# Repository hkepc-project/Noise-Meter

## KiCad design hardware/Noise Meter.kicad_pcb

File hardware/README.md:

This repository contains a Noise Meter project from the following link:

http://www.hkepc.com/forum/viewthread.php?fid=146&tid=2419038&extra=page%3D1

The hardware and associated materials (excluding any software) are provided under a [CC BY-SA 4.0](https://creativecommons.org/licenses/by-sa/4.0/) license.

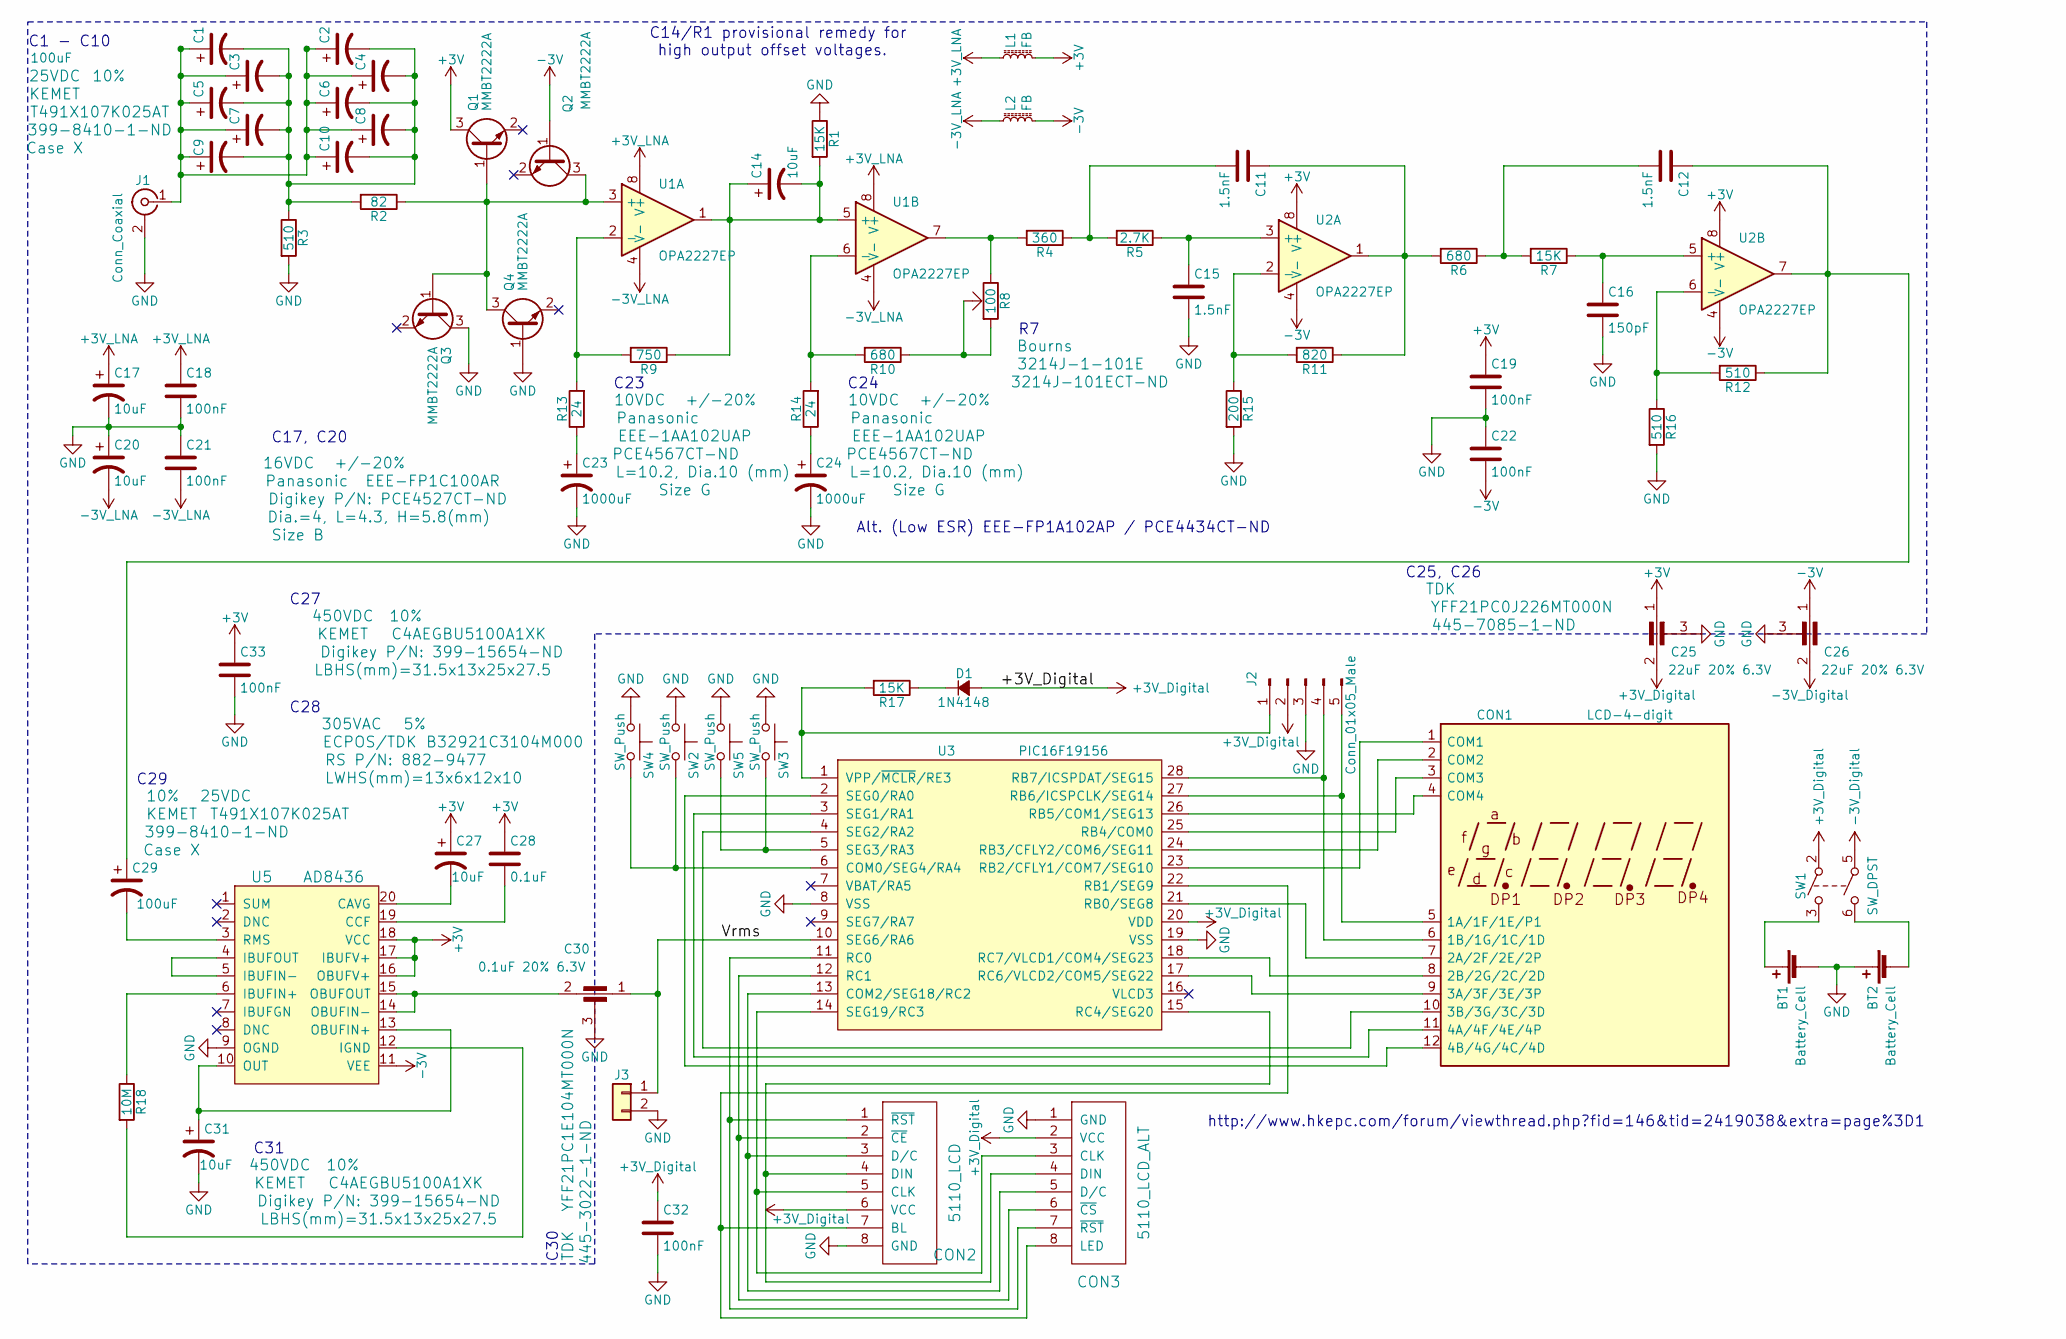
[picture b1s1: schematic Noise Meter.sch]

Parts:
BT1, BT2: Battery_Cell; Keystone_1058_1x2032-CoinCell
C1, C2, C3, C4, C5, C6, C7, C8, C9, C10, C29: 100uF; CP_Tantalum_Case-X_EIA-7343-43_Hand; Tolerance 10%; Voltage 25VDC; Manufacturer P/N T491X107K025AT; Digikey P/N 399-8410-1-ND
C11, C12, C15: 1.5nF; C_0603_HandSoldering
C14, C17, C20: 10uF; CP_Elec_4x4.5; Voltage 16VDC; Tolerance +/-20%; Manufacturer P/N EEE-FP1C100AR; Digikey P/N Digikey P/N: PCE4527CT-ND
C16: 150pF; C_0603_HandSoldering
C18, C19, C21, C22, C32, C33: 100nF; C_0603_HandSoldering
C23, C24: 1000uF; CP_Elec_10x10.5; Voltage 10VDC; Tolerance +/-20%; Manufacturer P/N EEE-1AA102UAP; Digikey P/N PCE4567CT-ND
C25, C26: 22uF 20% 6.3V; Feedthrough_C_0805_HandSoldering; Manufacturer P/N YFF21PC0J226MT000N; Digikey P/N 445-7085-1-ND
C27, C31: 10uF; C_Rect_L31.5mm_W13.0mm_P27.50mm_MKS4; Tolerance 10%; Voltage 450VDC; Manufacturer P/N C4AEGBU5100A1XK; Digikey P/N Digikey P/N: 399-15654-ND
C28: 0.1uF; C_Rect_L13.0mm_W6.0mm_P10.00mm_FKS3_FKP3_MKS4; Voltage 305VAC; Tolerance 5%
C30: 0.1uF 20% 6.3V; Feedthrough_C_0805_HandSoldering; Manufacturer P/N YFF21PC1E104MT000N; Digikey P/N 445-3022-1-ND
CON1: LCD-4-digit; 4-digit-LCD-footprint
CON2: 5110_LCD; 5110
CON3: 5110_LCD_ALT; 5110-Alt
D1: 1N4148; D_SOD-123
J1: Conn_Coaxial; SMA-CONN
J2: Conn_01x05_Male; Pin_Header_Angled_1x05_Pitch2.54mm
J3: Conn_01x02; Pin_Header_Angled_1x02_Pitch2.54mm
L1, L2: FB; L_0805
Q1, Q2, Q3, Q4: MMBT2222A; SOT-23
R1, R7, R17: 15K; R_0603_HandSoldering
R2: 82; R_0603_HandSoldering
R3, R12, R16: 510; R_0603_HandSoldering
R4: 360; R_0603_HandSoldering
R5: 2.7K; R_0603_HandSoldering
R6, R10: 680; R_0603_HandSoldering
R8: 100; Potentiometer_Trimmer_Bourns_3214J; Manufacturer P/N 3214J-1-101E; Digikey P/N 3214J-101ECT-ND
R9: 750; R_0603_HandSoldering
R11: 820; R_0603_HandSoldering
R13, R14: 24; R_0603_HandSoldering
R15: 200; R_0603_HandSoldering
R18: 10M; R_0603_HandSoldering
SW1: SW_DPST; SW_CuK_JS202011AQN_DPDT_Angled
SW2, SW3, SW4, SW5: SW_Push; SW_SPST_B3SL-1002P
U1, U2: OPA2227EP; SOIC-8-N
U3: PIC16F19156; SSOP-28_5.3x10.2mm_Pitch0.65mm
U5: AD8436; SSOP-20

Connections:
+3V: C19.1, C25.1, C27.1, C28.1, C33.1, L1.2, Q1.3 (C), U2.8 (V+), U5.16 (OBUFV+), U5.17 (IBUFV+), U5.18 (VCC)
+3V_Digital: C25.2, C32.1, CON2.6 (VCC), CON3.2 (VCC), D1.2 (A), J2.2, SW1.2, U3.20 (VDD)
+3V_LNA: C17.1, C18.1, L1.1, U1.8 (V+)
-3V: C22.2, C26.1, L2.2, Q2.1 (B), U2.4 (V-), U5.11 (VEE)
-3V_Digital: C26.2, SW1.5
-3V_LNA: C20.2, C21.2, L2.1, U1.4 (V-)
/Vrms: C30.1, J3.1, U3.10 (SEG6/RA6)
GND: BT1.2 (-), BT2.1 (+), C15.2, C16.2, C17.2, C18.2, C19.2, C20.1, C21.1, C22.1, C23.2, C24.2, C25.3, C26.3, C30.3, C31.2, C32.2, C33.2, CON2.8 (GND), CON3.1 (GND), J1.2 (Ext), J2.3, J3.2, Q3.3 (C), Q4.1 (B), R1.1, R3.2, R15.2, R16.2, SW2.1, SW3.1, SW4.1, SW5.1, U3.8 (VSS), U3.19 (VSS), U5.9 (OGND)
unnamed: BT1.1 (+), SW1.3
unnamed: BT2.2 (-), SW1.6
unnamed: C1.1, C2.1, C3.1, C4.1, C5.1, C6.1, C7.1, C8.1, C9.1, C10.1, J1.1 (In)
unnamed: C1.2, C2.2, C3.2, C4.2, C5.2, C6.2, C7.2, C8.2, C9.2, C10.2, R2.2, R3.1
unnamed: C11.1, R6.2, R11.1, U2.1
unnamed: C11.2, R4.1, R5.2
unnamed: C12.1, C29.1, R12.1, U2.7
unnamed: C12.2, R6.1, R7.2
unnamed: C14.1, C14.2, R1.2, R9.1, U1.1, U1.5 (+)
unnamed: C15.1, R5.1, U2.3 (+)
unnamed: C16.1, R7.1, U2.5 (+)
unnamed: C23.1, R13.1
unnamed: C24.1, R14.1
unnamed: C27.2, U5.20 (CAVG)
unnamed: C28.2, U5.19 (CCF)
unnamed: C29.2, U5.3 (RMS)
unnamed: C30.2, U5.14 (OBUFIN-), U5.15 (OBUFOUT)
unnamed: C31.1, U5.10 (OUT), U5.13 (OBUFIN+)
unnamed: CON1.1 (COM1), U3.23 (RB2/CFLY1/COM7/SEG10)
unnamed: CON1.2 (COM2), U3.24 (RB3/CFLY2/COM6/SEG11)
unnamed: CON1.3 (COM3), U3.25 (RB4/COM0)
unnamed: CON1.4 (COM4), U3.26 (RB5/COM1/SEG13)
unnamed: CON1.5 (1A/1F/1E/P1), J2.5, U3.27 (RB6/ICSPCLK/SEG14)
unnamed: CON1.6 (1B/1G/1C/1D), J2.4, U3.28 (RB7/ICSPDAT/SEG15)
unnamed: CON1.7 (2A/2F/2E/2P), U3.21 (RB0/SEG8)
unnamed: CON1.8 (2B/2G/2C/2D), U3.18 (RC7/VLCD1/COM4/SEG23)
unnamed: CON1.9 (3A/3F/3E/3P), U3.17 (RC6/VLCD2/COM5/SEG22)
unnamed: CON1.10 (3B/3G/3C/3D), U3.4 (SEG2/RA2)
unnamed: CON1.11 (4A/4F/4E/4P), U3.3 (SEG1/RA1)
unnamed: CON1.12 (4B/4G/4C/4D), U3.2 (SEG0/RA0)
unnamed: CON2.1 (~RST), CON3.7 (~RST), U3.11 (RC0)
unnamed: CON2.2 (~CE), CON3.6 (~CS), U3.12 (RC1)
unnamed: CON2.3 (D/C), CON3.5 (D/C), U3.13 (COM2/SEG18/RC2)
unnamed: CON2.4 (DIN), CON3.4 (DIN), U3.15 (RC4/SEG20)
unnamed: CON2.5 (CLK), CON3.3 (CLK), U3.14 (SEG19/RC3)
unnamed: CON2.7 (BL), CON3.8 (LED), U3.22 (RB1/SEG9)
unnamed: D1.1 (K), R17.1
unnamed: J2.1, R17.2, U3.1 (VPP/~MCLR~/RE3)
unnamed: Q1.1 (B), Q2.3 (C), Q3.1 (B), Q4.3 (C), R2.1, U1.3 (+)
unnamed: R4.2, R8.1, U1.7
unnamed: R8.2, R8.3, R10.1
unnamed: R10.2, R14.2, U1.6 (-)
unnamed: R11.2, R15.1, U2.2 (-)
unnamed: R12.2, R16.1, U2.6 (-)
unnamed: R9.2, R13.2, U1.2 (-)
unnamed: R18.1, U5.6 (IBUFIN+)
unnamed: R18.2, U5.12 (IGND)
unnamed: SW2.2, SW4.2, U3.6 (COM0/SEG4/RA4)
unnamed: SW3.2, SW5.2, U3.5 (SEG3/RA3)
unnamed: U5.4 (IBUFOUT), U5.5 (IBUFIN-)

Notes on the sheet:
C27
C28
C29
Alt. (Low ESR) EEE-FP1A102AP / PCE4434CT-ND
C17, C20
C31
C24
C23
C25, C26
C30
C1 - C10
C14/R1 provisional remedy for high output offset voltages.
http://www.hkepc.com/forum/viewthread.php?fid=146&tid=2419038&extra=page%3D1

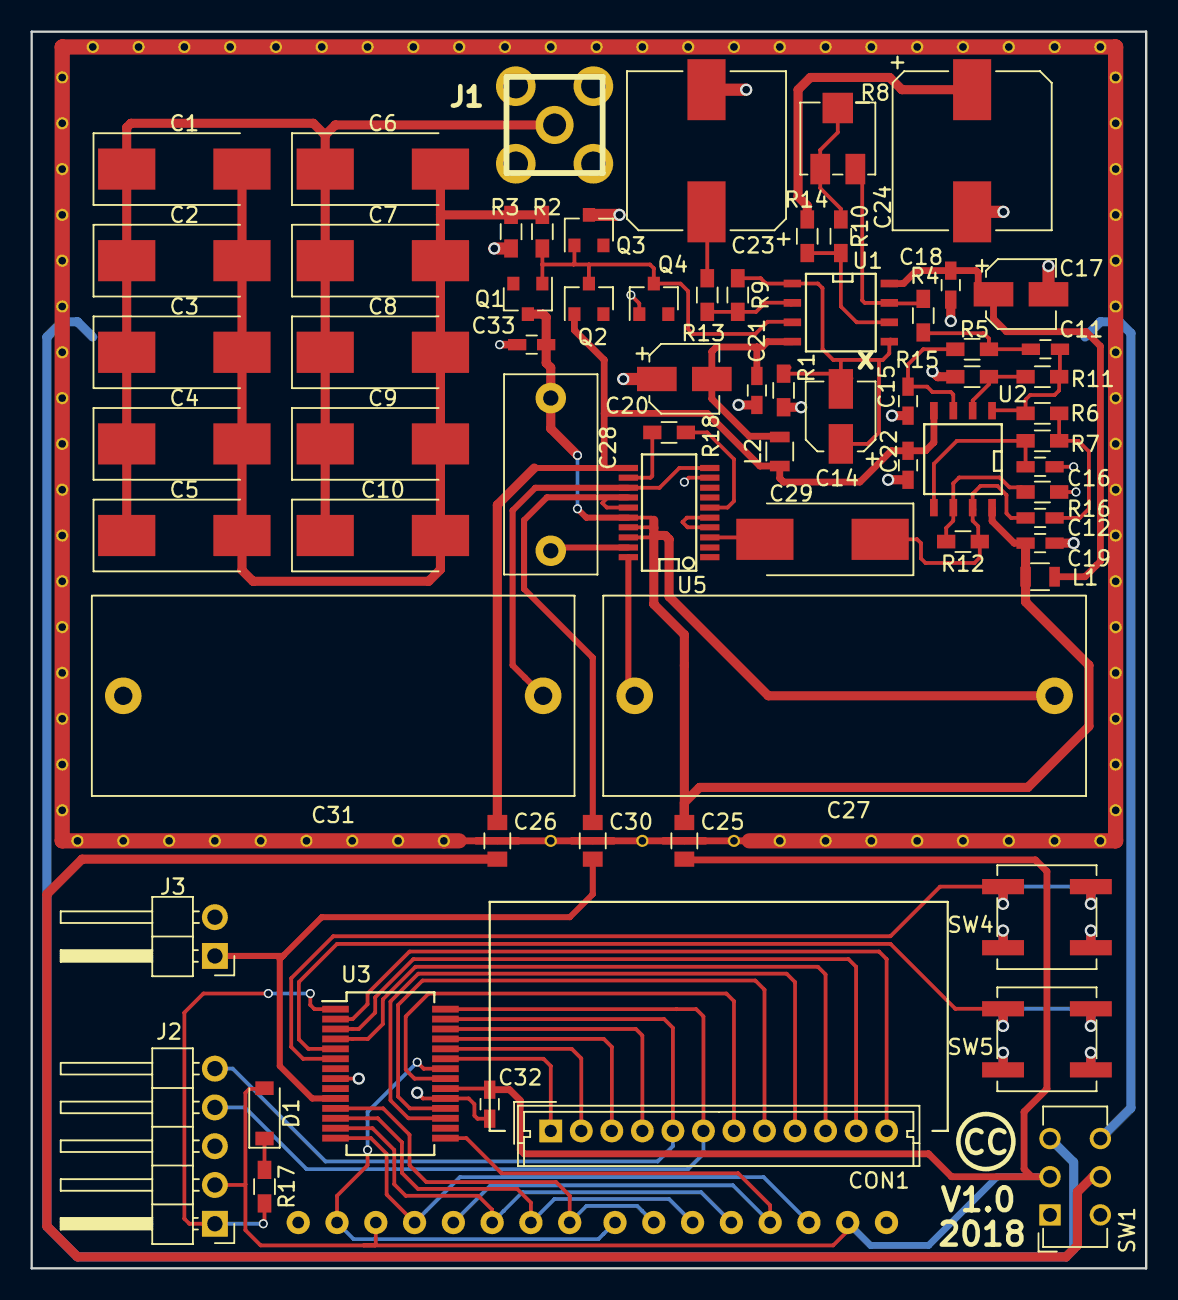
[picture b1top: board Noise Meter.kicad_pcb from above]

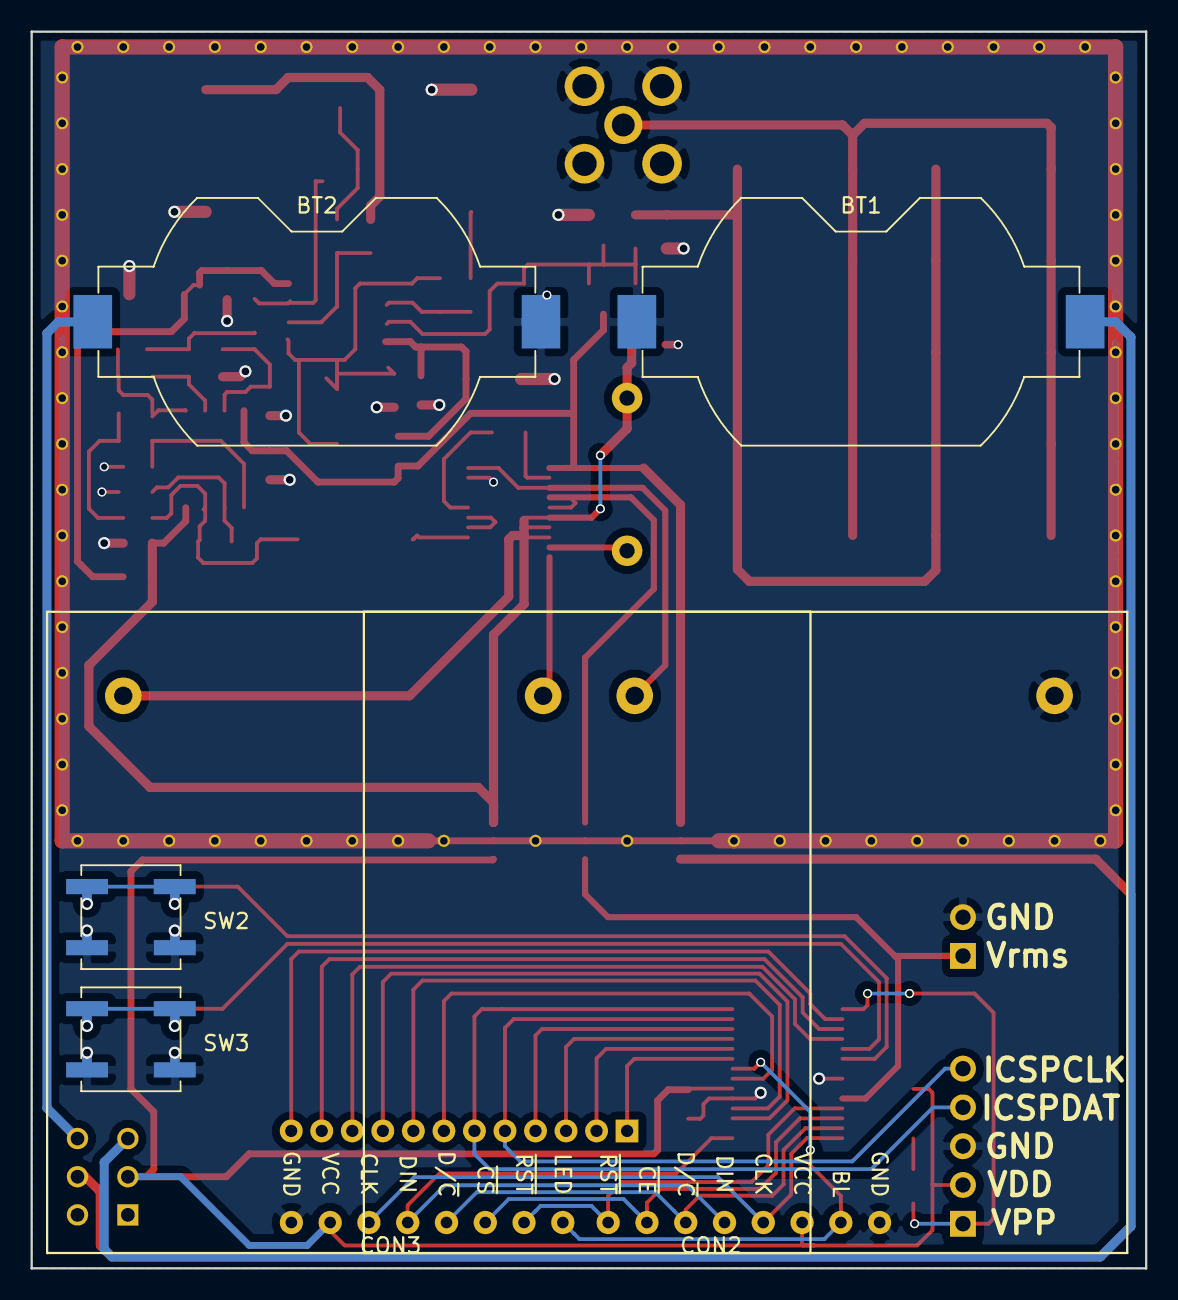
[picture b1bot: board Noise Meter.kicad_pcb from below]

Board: 2 copper layers, 73.0 x 81.0 mm, 74 parts (6 on the bottom side), 58 nets.

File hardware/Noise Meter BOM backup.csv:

Ref,Qty,Value,Footprint,Datasheet,Digikey P/N,EIA Case Code,Manufacturer,Manufacturer P/N,Mnaufacturer P/N,Size,Size Code,Szie,Tolerance,Vendor P/N,Voltage
Title,,,,,,,,,,,,,,,
Revision,,,,,,,,,,,,,,,
Date,,,,,,,,,,,,,,,
Generated,2018-02-01 23:53:58,,,,,,,,,,,,,,
Company,,,,,,,,,,,,,,,
Comment 1,,,,,,,,,,,,,,,
Comment 2,,,,,,,,,,,,,,,
Comment 3,,,,,,,,,,,,,,,
Comment 4,,,,,,,,,,,,,,,
Total Parts,74,,,,,,,,,,,,,,
Total Unique Parts,37,,,,,,,,,,,,,,
,,,,,,,,,,,,,,,
,,,,,,,,,,,,,,,
,,,,,,,,,,,,,,,
Ref,Qty,Value,Footprint,Datasheet,Digikey P/N,EIA Case Code,Manufacturer,Manufacturer P/N,Mnaufacturer P/N,Size,Size Code,Szie,Tolerance,Vendor P/N,Voltage
BT1 BT2 ,2,Battery_Cell,Battery_Holders:Keystone_1058_1x2032-CoinCell,, , , , , , , , , , , 
C1 C2 C3 C4 C5 C6 C7 C8 C9 C10 C29 ,11,100uF,Capacitors_Tantalum_SMD:CP_Tantalum_Case-X_EIA-7343-43_Hand,https://content.kemet.com/datasheets/KEM_T2005_T491.pdf,399-8410-1-ND,,KEMET,T491X107K025AT, , ,Case X, ,10%, ,25VDC
C11 C12 C15 ,3,1.5nF,Capacitors_SMD:C_0603_HandSoldering,, , , , , , , , , , , 
C14 C17 C20 ,3,10uF,Capacitors_SMD:CP_Elec_4x4.5,https://industrial.panasonic.com/cdbs/www-data/pdf/RDE0000/A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,PCE4527CT-ND, ,Panasonic,EEE-FP1C100AR, ,Dia.=4  L=4.3  H=5.8(mm),Size B, ,+/-20%, ,16VDC
C16 ,1,150pF,Capacitors_SMD:C_0603_HandSoldering,, , , , , , , , , , , 
C18 C19 C21 C22 C32 C33 ,6,100nF,Capacitors_SMD:C_0603_HandSoldering,, , , , , , , , , , , 
C23 C24 ,2,1000uF,Capacitors_SMD:CP_Elec_10x10.5,https://industrial.panasonic.com/cdbs/www-data/pdf/RDE0000/A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,PCE4567CT-ND, ,Panasonic,EEE-1AA102UAP, , ,Size G,L=10.2  Dia.10 (mm),+/-20%, ,10VDC
C25 C26 ,2,22uF 20% 6.3V,Noise Meter Kicad Footprint Library:Feedthrough_C_0805_HandSoldering,,445-7085-1-ND, ,TDK,YFF21PC0J226MT000N, , , , , , , 
C27 C31 ,2,10uF,Capacitors_THT:C_Rect_L31.5mm_W13.0mm_P27.50mm_MKS4,https://content.kemet.com/datasheets/KEM_F3103_R60.pdf,399-15654-ND, ,KEMET,C4AEGBU5100A1XK, ,LBHS(mm)=31.5x13x25x27.5, , ,10%, ,450VDC
C28 ,1,0.1uF,Capacitors_THT:C_Rect_L13.0mm_W6.0mm_P10.00mm_FKS3_FKP3_MKS4,https://en.tdk.eu/inf/20/20/db/fc_2009/X2_B32921_928.pdf, , ,ECPOS/TDK,B32921C3104M000,,LWHS(mm)=13x6x12x10, , ,5%,RS P/N: 882-9477,305VAC
C30 ,1,0.1uF 20% 6.3V,Noise Meter Kicad Footprint Library:Feedthrough_C_0805_HandSoldering,https://product.tdk.com/info/en/catalog/datasheets/3tf_comme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,445-3022-1-ND, ,TDK,YFF21PC1E104MT000N, , , , , , , 
CON1 ,1,LCD-4-digit,Noise Meter Kicad Footprint Library:4-digit-LCD-footprint,, , , , , , , , , , , 
CON2 ,1,5110_LCD,Noise Meter Kicad Footprint Library:5110,, , , , , , , , , , , 
CON3 ,1,5110_LCD_ALT,Noise Meter Kicad Footprint Library:5110-Alt,, , , , , , , , , , , 
D1 ,1,1N4148,Diodes_SMD:D_SOD-123,, , , , , , , , , , , 
J1 ,1,Conn_Coaxial,Noise Meter Kicad Footprint Library:SMA-CONN,, , , , , , , , , , , 
J2 ,1,Conn_01x05_Male,Pin_Headers:Pin_Header_Angled_1x05_Pitch2.54mm,, , , , , , , , , , , 
J3 ,1,Conn_01x02,Pin_Headers:Pin_Header_Angled_1x02_Pitch2.54mm,, , , , , , , , , , , 
L1 L2 ,2,FB,Inductors_SMD:L_0805,, , , , , , , , , , , 
Q1 Q2 Q3 Q4 ,4,MMBT2222A,TO_SOT_Packages_SMD:SOT-23,, , , , , , , , , , , 
R1 R7 R17 ,3,15K,Resistors_SMD:R_0603_HandSoldering,, , , , , , , , , , , 
R2 ,1,82,Resistors_SMD:R_0603_HandSoldering,, , , , , , , , , , , 
R3 R12 R16 ,3,510,Resistors_SMD:R_0603_HandSoldering,, , , , , , , , , , , 
R4 ,1,360,Resistors_SMD:R_0603_HandSoldering,, , , , , , , , , , , 
R5 ,1,2.7K,Resistors_SMD:R_0603_HandSoldering,, , , , , , , , , , , 
R6 R10 ,2,680,Resistors_SMD:R_0603_HandSoldering,, , , , , , , , , , , 
R8 ,1,100,Potentiometers:Potentiometer_Trimmer_Bourns_3214J,http://www.bourns.com/docs/Product-Datasheets/3214.pdf,3214J-101ECT-ND, ,Bourns,3214J-1-101E, , , , , , , 
R9 ,1,750,Resistors_SMD:R_0603_HandSoldering,, , , , , , , , , , , 
R11 ,1,820,Resistors_SMD:R_0603_HandSoldering,, , , , , , , , , , , 
R13 R14 ,2,24,Resistors_SMD:R_0603_HandSoldering,, , , , , , , , , , , 
R15 ,1,200,Resistors_SMD:R_0603_HandSoldering,, , , , , , , , , , , 
R18 ,1,10M,Resistors_SMD:R_0603_HandSoldering,, , , , , , , , , , , 
SW1 ,1,SW_DPST,Buttons_Switches_THT:SW_CuK_JS202011AQN_DPDT_Angled,, , , , , , , , , , , 
SW2 SW3 SW4 SW5 ,4,SW_Push,Buttons_Switches_SMD:SW_SPST_B3SL-1002P,, , , , , , , , , , , 
U1 U2 ,2,OPA2227EP,SMD_Packages:SOIC-8-N,,, , TI,OPA2227EP,, , , ,,, 
U3 ,1,PIC16F19156,Housings_SSOP:SSOP-28_5.3x10.2mm_Pitch0.65mm,, , ,microchip,PIC16F19156,, , , ,,, 
U5 ,1,AD8436,SMD_Packages:SSOP-20,, , ,analog,AD8436,, , , ,,, 
,,,,,,,,,,,,,,,
,,,,,,,,,,,,,,,
,,,,,,,,,,,,,,,
,,,,,,,,,,,,,,,
BOM made with KICAD_BOM_WIZARD (https://github.com/HashDefineElectronics/KiCad_BOM_Wizard.git),,,,,,,,,,,,,,,
Generated 2018-02-01 23:53:58,,,,,,,,,,,,,,,

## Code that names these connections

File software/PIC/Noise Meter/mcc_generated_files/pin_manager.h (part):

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// get/set SW_ODD aliases
#define SW_ODD_TRIS               TRISAbits.TRISA3
#define SW_ODD_LAT                LATAbits.LATA3
#define SW_ODD_PORT               PORTAbits.RA3
#define SW_ODD_WPU                WPUAbits.WPUA3
#define SW_ODD_OD                ODCONAbits.ODCA3
#define SW_ODD_ANS                ANSELAbits.ANSA3
#define SW_ODD_SetHigh()            do { LATAbits.LATA3 = 1; } while(0)
#define SW_ODD_SetLow()             do { LATAbits.LATA3 = 0; } while(0)
#define SW_ODD_Toggle()             do { LATAbits.LATA3 = ~LATAbits.LATA3; } while(0)
#define SW_ODD_GetValue()           PORTAbits.RA3
#define SW_ODD_SetDigitalInput()    do { TRISAbits.TRISA3 = 1; } while(0)
#define SW_ODD_SetDigitalOutput()   do { TRISAbits.TRISA3 = 0; } while(0)
#define SW_ODD_SetPullup()      do { WPUAbits.WPUA3 = 1; } while(0)
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// get/set SW_EVEN aliases
#define SW_EVEN_TRIS               TRISAbits.TRISA4
#define SW_EVEN_LAT                LATAbits.LATA4
#define SW_EVEN_PORT               PORTAbits.RA4
#define SW_EVEN_WPU                WPUAbits.WPUA4
#define SW_EVEN_OD                ODCONAbits.ODCA4
#define SW_EVEN_ANS                ANSELAbits.ANSA4
#define SW_EVEN_SetHigh()            do { LATAbits.LATA4 = 1; } while(0)
#define SW_EVEN_SetLow()             do { LATAbits.LATA4 = 0; } while(0)
#define SW_EVEN_Toggle()             do { LATAbits.LATA4 = ~LATAbits.LATA4; } while(0)
#define SW_EVEN_GetValue()           PORTAbits.RA4
#define SW_EVEN_SetDigitalInput()    do { TRISAbits.TRISA4 = 1; } while(0)
#define SW_EVEN_SetDigitalOutput()   do { TRISAbits.TRISA4 = 0; } while(0)
#define SW_EVEN_SetPullup()      do { WPUAbits.WPUA4 = 1; } while(0)
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// get/set channel_ANA6 aliases
#define channel_ANA6_TRIS               TRISAbits.TRISA6
#define channel_ANA6_LAT                LATAbits.LATA6
#define channel_ANA6_PORT               PORTAbits.RA6
#define channel_ANA6_WPU                WPUAbits.WPUA6
#define channel_ANA6_OD                ODCONAbits.ODCA6
#define channel_ANA6_ANS                ANSELAbits.ANSA6
#define channel_ANA6_SetHigh()            do { LATAbits.LATA6 = 1; } while(0)
#define channel_ANA6_SetLow()             do { LATAbits.LATA6 = 0; } while(0)
#define channel_ANA6_Toggle()             do { LATAbits.LATA6 = ~LATAbits.LATA6; } while(0)
#define channel_ANA6_GetValue()           PORTAbits.RA6
#define channel_ANA6_SetDigitalInput()    do { TRISAbits.TRISA6 = 1; } while(0)
#define channel_ANA6_SetDigitalOutput()   do { TRISAbits.TRISA6 = 0; } while(0)
#define channel_ANA6_SetPullup()      do { WPUAbits.WPUA6 = 1; } while(0)
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#define RB0_SetHigh()    do { LATBbits.LATB0 = 1; } while(0)
#define RB0_SetLow()   do { LATBbits.LATB0 = 0; } while(0)
#define RB0_Toggle()   do { LATBbits.LATB0 = ~LATBbits.LATB0; } while(0)
#define RB0_GetValue()         PORTBbits.RB0
#define RB0_SetDigitalInput()   do { TRISBbits.TRISB0 = 1; } while(0)
#define RB0_SetDigitalOutput()  do { TRISBbits.TRISB0 = 0; } while(0)
#define RB0_SetPullup()     do { WPUBbits.WPUB0 = 1; } while(0)
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// get/set LCD_BL aliases
#define LCD_BL_TRIS               TRISBbits.TRISB1
#define LCD_BL_LAT                LATBbits.LATB1
#define LCD_BL_PORT               PORTBbits.RB1
#define LCD_BL_WPU                WPUBbits.WPUB1
#define LCD_BL_OD                ODCONBbits.ODCB1
#define LCD_BL_ANS                ANSELBbits.ANSB1
#define LCD_BL_SetHigh()            do { LATBbits.LATB1 = 1; } while(0)
#define LCD_BL_SetLow()             do { LATBbits.LATB1 = 0; } while(0)
#define LCD_BL_Toggle()             do { LATBbits.LATB1 = ~LATBbits.LATB1; } while(0)
#define LCD_BL_GetValue()           PORTBbits.RB1
#define LCD_BL_SetDigitalInput()    do { TRISBbits.TRISB1 = 1; } while(0)
#define LCD_BL_SetDigitalOutput()   do { TRISBbits.TRISB1 = 0; } while(0)
#define LCD_BL_SetPullup()      do { WPUBbits.WPUB1 = 1; } while(0)
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// get/set LCD_RST aliases
#define LCD_RST_TRIS               TRISCbits.TRISC0
#define LCD_RST_LAT                LATCbits.LATC0
#define LCD_RST_PORT               PORTCbits.RC0
#define LCD_RST_WPU                WPUCbits.WPUC0
#define LCD_RST_OD                ODCONCbits.ODCC0
#define LCD_RST_SetHigh()            do { LATCbits.LATC0 = 1; } while(0)
#define LCD_RST_SetLow()             do { LATCbits.LATC0 = 0; } while(0)
#define LCD_RST_Toggle()             do { LATCbits.LATC0 = ~LATCbits.LATC0; } while(0)
#define LCD_RST_GetValue()           PORTCbits.RC0
#define LCD_RST_SetDigitalInput()    do { TRISCbits.TRISC0 = 1; } while(0)
#define LCD_RST_SetDigitalOutput()   do { TRISCbits.TRISC0 = 0; } while(0)
#define LCD_RST_SetPullup()      do { WPUCbits.WPUC0 = 1; } while(0)
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// get/set LCD_CE aliases
#define LCD_CE_TRIS               TRISCbits.TRISC1
#define LCD_CE_LAT                LATCbits.LATC1
#define LCD_CE_PORT               PORTCbits.RC1
#define LCD_CE_WPU                WPUCbits.WPUC1
#define LCD_CE_OD                ODCONCbits.ODCC1
#define LCD_CE_SetHigh()            do { LATCbits.LATC1 = 1; } while(0)
#define LCD_CE_SetLow()             do { LATCbits.LATC1 = 0; } while(0)
#define LCD_CE_Toggle()             do { LATCbits.LATC1 = ~LATCbits.LATC1; } while(0)
#define LCD_CE_GetValue()           PORTCbits.RC1
#define LCD_CE_SetDigitalInput()    do { TRISCbits.TRISC1 = 1; } while(0)
#define LCD_CE_SetDigitalOutput()   do { TRISCbits.TRISC1 = 0; } while(0)
#define LCD_CE_SetPullup()      do { WPUCbits.WPUC1 = 1; } while(0)
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// get/set LCD_DC aliases
#define LCD_DC_TRIS               TRISCbits.TRISC2
#define LCD_DC_LAT                LATCbits.LATC2
#define LCD_DC_PORT               PORTCbits.RC2
#define LCD_DC_WPU                WPUCbits.WPUC2
#define LCD_DC_OD                ODCONCbits.ODCC2
#define LCD_DC_ANS                ANSELCbits.ANSC2
#define LCD_DC_SetHigh()            do { LATCbits.LATC2 = 1; } while(0)
#define LCD_DC_SetLow()             do { LATCbits.LATC2 = 0; } while(0)
#define LCD_DC_Toggle()             do { LATCbits.LATC2 = ~LATCbits.LATC2; } while(0)
#define LCD_DC_GetValue()           PORTCbits.RC2
#define LCD_DC_SetDigitalInput()    do { TRISCbits.TRISC2 = 1; } while(0)
#define LCD_DC_SetDigitalOutput()   do { TRISCbits.TRISC2 = 0; } while(0)
#define LCD_DC_SetPullup()      do { WPUCbits.WPUC2 = 1; } while(0)
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// get/set LCD_CLK aliases
#define LCD_CLK_TRIS               TRISCbits.TRISC3
#define LCD_CLK_LAT                LATCbits.LATC3
#define LCD_CLK_PORT               PORTCbits.RC3
#define LCD_CLK_WPU                WPUCbits.WPUC3
#define LCD_CLK_OD                ODCONCbits.ODCC3
#define LCD_CLK_ANS                ANSELCbits.ANSC3
#define LCD_CLK_SetHigh()            do { LATCbits.LATC3 = 1; } while(0)
#define LCD_CLK_SetLow()             do { LATCbits.LATC3 = 0; } while(0)
#define LCD_CLK_Toggle()             do { LATCbits.LATC3 = ~LATCbits.LATC3; } while(0)
#define LCD_CLK_GetValue()           PORTCbits.RC3
#define LCD_CLK_SetDigitalInput()    do { TRISCbits.TRISC3 = 1; } while(0)
#define LCD_CLK_SetDigitalOutput()   do { TRISCbits.TRISC3 = 0; } while(0)
#define LCD_CLK_SetPullup()      do { WPUCbits.WPUC3 = 1; } while(0)
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// get/set LCD_DIN aliases
#define LCD_DIN_TRIS               TRISCbits.TRISC4
#define LCD_DIN_LAT                LATCbits.LATC4
#define LCD_DIN_PORT               PORTCbits.RC4
#define LCD_DIN_WPU                WPUCbits.WPUC4
#define LCD_DIN_OD                ODCONCbits.ODCC4
#define LCD_DIN_ANS                ANSELCbits.ANSC4
#define LCD_DIN_SetHigh()            do { LATCbits.LATC4 = 1; } while(0)
#define LCD_DIN_SetLow()             do { LATCbits.LATC4 = 0; } while(0)
#define LCD_DIN_Toggle()             do { LATCbits.LATC4 = ~LATCbits.LATC4; } while(0)
#define LCD_DIN_GetValue()           PORTCbits.RC4
#define LCD_DIN_SetDigitalInput()    do { TRISCbits.TRISC4 = 1; } while(0)
#define LCD_DIN_SetDigitalOutput()   do { TRISCbits.TRISC4 = 0; } while(0)
#define LCD_DIN_SetPullup()      do { WPUCbits.WPUC4 = 1; } while(0)
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
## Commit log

2018-01-19 with LICENSE
2018-01-20 ready for pcb layout
2018-01-21 License modified
2018-01-27 PCB V1.0
2018-01-27 final touch ups and gerber files added
2018-01-29 first pcb fabrication version
2018-04-25 ADC testing in porgress...
2018-04-25 First Working Version
2018-04-26 test....

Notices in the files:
software/PIC/Noise Meter/mcc_generated_files/pin_manager.h:
Copyright (c) 2013 - 2015 released Microchip Technology Inc.  All rights reserved.
